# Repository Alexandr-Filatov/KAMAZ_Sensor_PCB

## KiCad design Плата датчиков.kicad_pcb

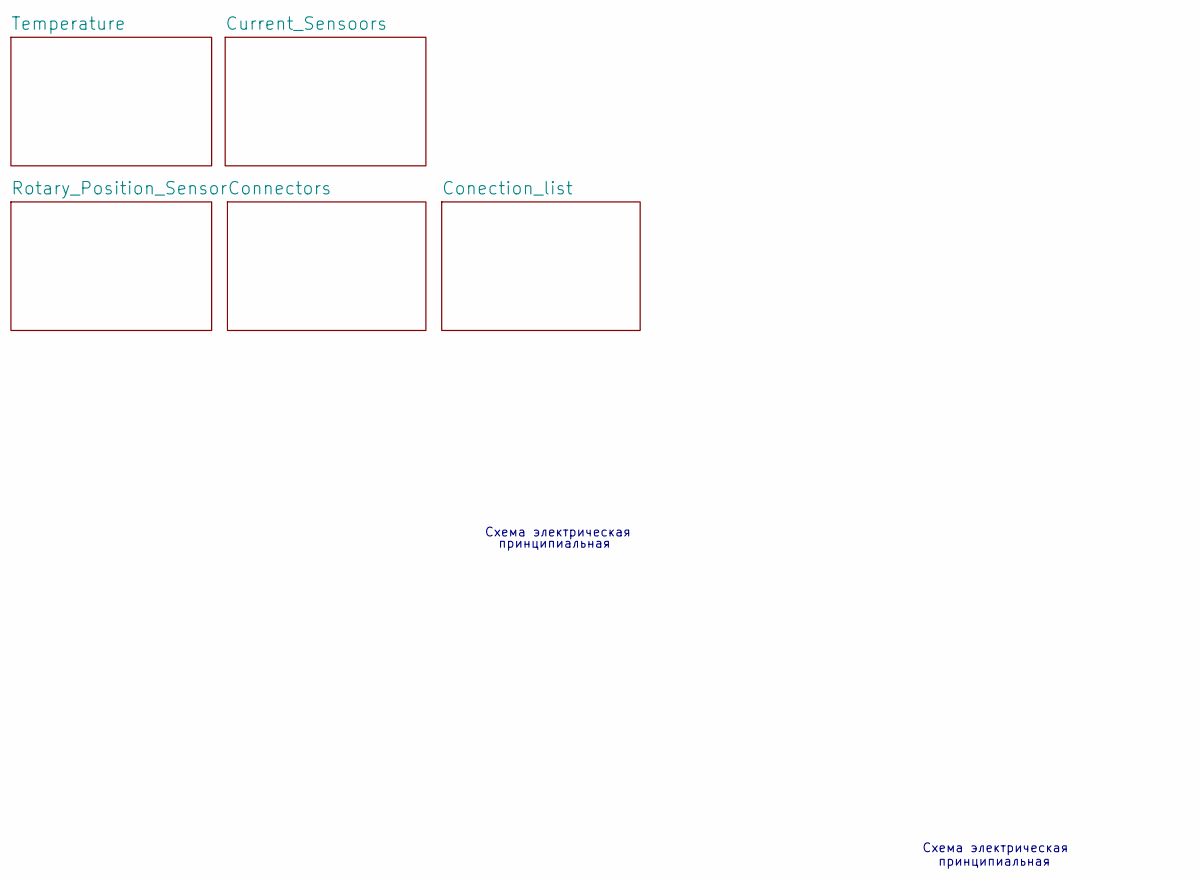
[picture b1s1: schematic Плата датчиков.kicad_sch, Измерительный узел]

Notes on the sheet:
Схема электрическая
принципиальная
Схема электрическая
принципиальная

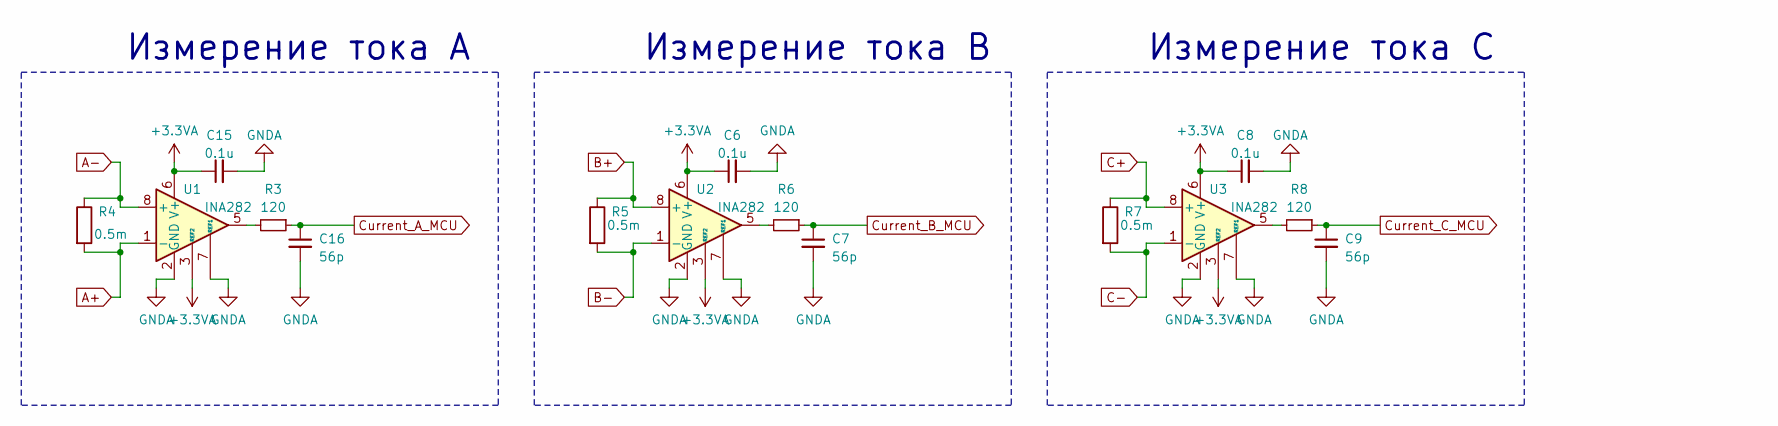
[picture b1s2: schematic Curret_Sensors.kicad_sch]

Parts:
C6, C8, C15: 0.1u; C_0603_1608Metric_Pad1.08x0.95mm_HandSolder
C7, C9, C16: 56p; C_0603_1608Metric_Pad1.08x0.95mm_HandSolder
R3, R6, R8: 120; R_0603_1608Metric_Pad0.98x0.95mm_HandSolder
R4, R5, R7: 0.5m; R_2512_6332Metric_Pad1.40x3.35mm_HandSolder
U1, U2, U3: INA282; SOIC-8_3.9x4.9mm_P1.27mm

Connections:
+3.3VA: C6.1, C8.1, C15.1, U1.3 (REF2), U1.6 (V+), U2.3 (REF2), U2.6 (V+), U3.3 (REF2), U3.6 (V+); also elsewhere on the board
A+: R4.2, U1.1 (-); also elsewhere on the board
A-: R4.1, U1.8 (+); also elsewhere on the board
B+: R5.1, U2.8 (+); also elsewhere on the board
B-: R5.2, U2.1 (-); also elsewhere on the board
C+: R7.1, U3.8 (+); also elsewhere on the board
C-: R7.2, U3.1 (-); also elsewhere on the board
Current_A_MCU: C16.1, R3.1; also elsewhere on the board
Current_B_MCU: C7.1, R6.1; also elsewhere on the board
Current_C_MCU: C9.1, R8.1; also elsewhere on the board
GNDA: C6.2, C7.2, C8.2, C9.2, C15.2, C16.2, U1.2 (GND), U1.7 (REF1), U2.2 (GND), U2.7 (REF1), U3.2 (GND), U3.7 (REF1); also elsewhere on the board
unnamed: R3.2, U1.5
unnamed: R6.2, U2.5
unnamed: R8.2, U3.5

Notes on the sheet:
Измерение тока В
Измерение тока А
Измерение тока С

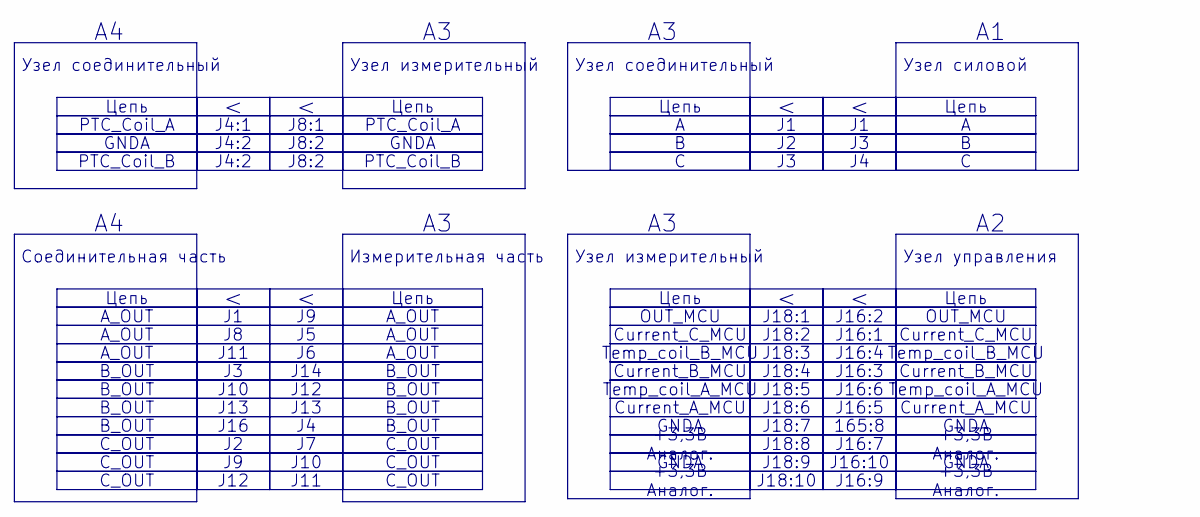
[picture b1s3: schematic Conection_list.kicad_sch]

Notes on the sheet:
J16
PTC_Coil_B
GNDA
Цепь
J18:4
165:8
J8:1
B_OUT
J18:10
J16:3
Current_B_MCU
J4:2
A_OUT
J16:5
OUT_MCU
Current_A_MCU
J16:9
J16:10
J18:8
J13
J10
PTC_Coil_A
J16:4
J12
+3,3В Аналог.
C_OUT
J11
J18:6
J18:5
J18:7
J12
J4:1
J8:2
Current_C_MCU
J16:6
Temp_coil_B_MCU
J10
J18:9
J18:2
J16:2

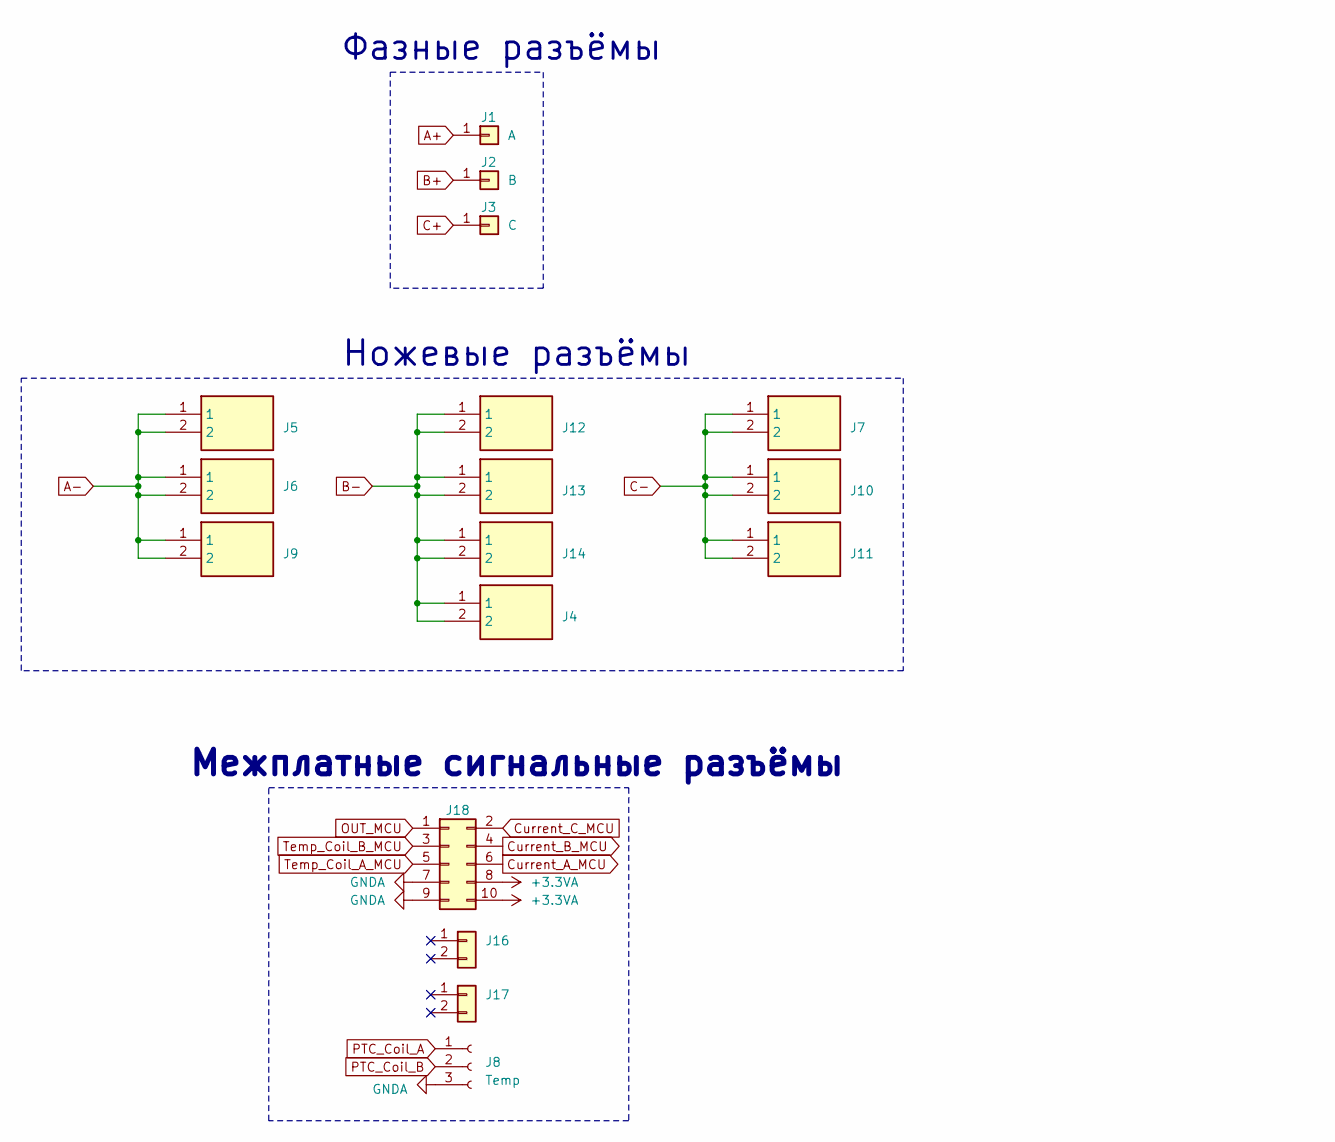
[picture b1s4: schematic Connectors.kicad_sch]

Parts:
J1: A; Power_Wire
J2: B; Power_Wire
J3: C; Power_Wire
J4, J5, J6, J7, J9, J10, J11, J12, J13, J14: 4900; Manufacturer_Part_Number 4900; Mouser Part Number 534-4900
J8: Temp; PinHeader_1x03_P2.54mm_Vertical
J16, J17: Conn_01x02; PinHeader_1x02_P1.27mm_Vertical
J18: Conn_02x05_Odd_Even; PinHeader_2x05_P1.27mm_Vertical

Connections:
+3.3VA: J18.8, J18.10; also elsewhere on the board
A+: J1.1; also elsewhere on the board
A-: J5.1, J5.2, J6.1, J6.2, J9.1, J9.2; also elsewhere on the board
B+: J2.1; also elsewhere on the board
B-: J4.1, J4.2, J12.1, J12.2, J13.1, J13.2, J14.1, J14.2; also elsewhere on the board
C+: J3.1; also elsewhere on the board
C-: J7.1, J7.2, J10.1, J10.2, J11.1, J11.2; also elsewhere on the board
Current_A_MCU: J18.6; also elsewhere on the board
Current_B_MCU: J18.4; also elsewhere on the board
Current_C_MCU: J18.2; also elsewhere on the board
GNDA: J8.3, J18.7, J18.9; also elsewhere on the board
OUT_MCU: J18.1; also elsewhere on the board
PTC_Coil_A: J8.1; also elsewhere on the board
PTC_Coil_B: J8.2; also elsewhere on the board
Temp_Coil_A_MCU: J18.5; also elsewhere on the board
Temp_Coil_B_MCU: J18.3; also elsewhere on the board

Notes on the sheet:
Межплатные сигнальные разъёмы
Фазные разъёмы
Ножевые разъёмы

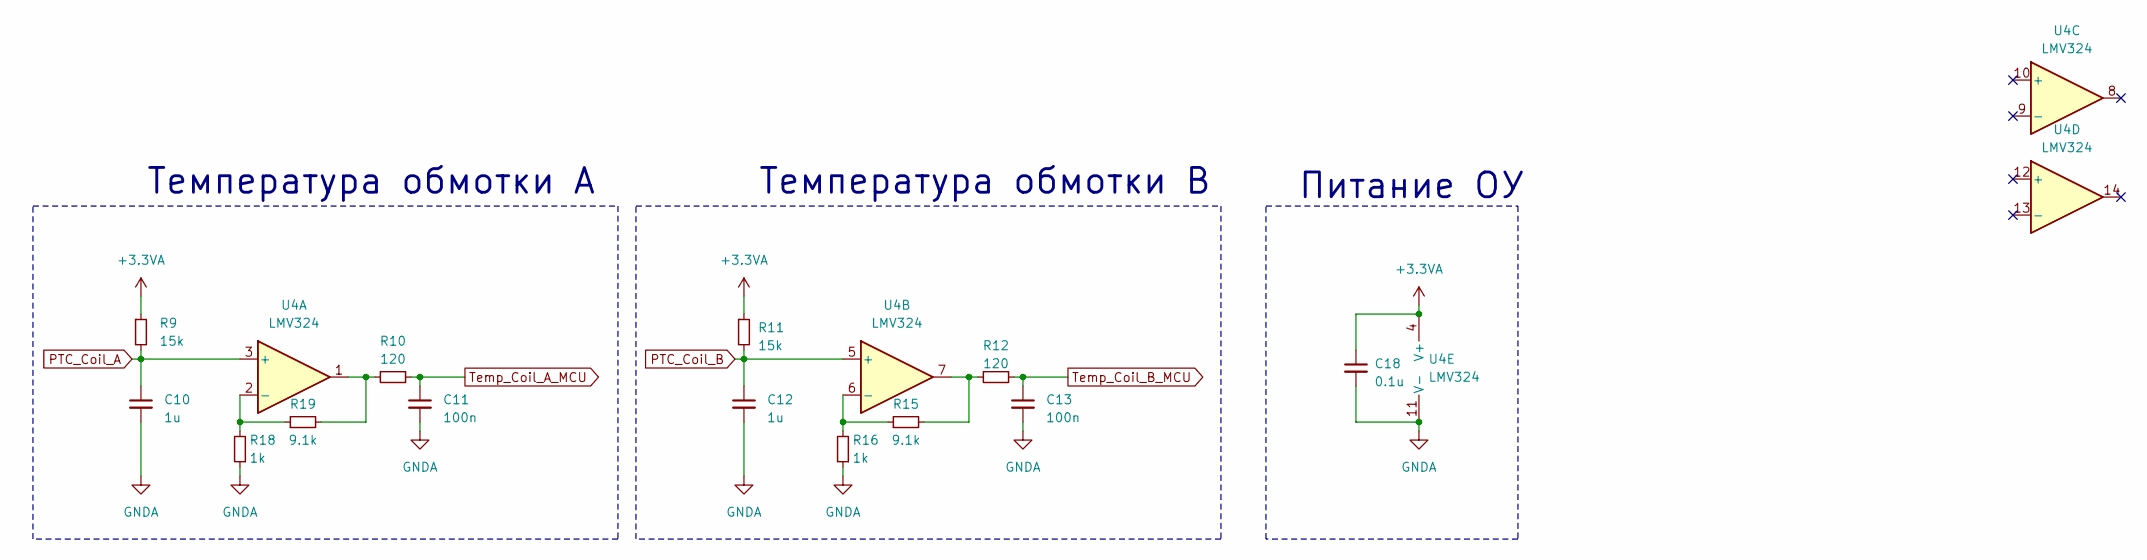
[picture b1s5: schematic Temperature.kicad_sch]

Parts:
C10, C12: 1u; C_0603_1608Metric_Pad1.08x0.95mm_HandSolder
C11, C13: 100n; C_0603_1608Metric_Pad1.08x0.95mm_HandSolder
C18: 0.1u; C_0603_1608Metric_Pad1.08x0.95mm_HandSolder
R9, R11: 15k; R_0603_1608Metric_Pad0.98x0.95mm_HandSolder
R10, R12: 120; R_0603_1608Metric_Pad0.98x0.95mm_HandSolder
R15, R19: 9.1k; R_0603_1608Metric_Pad0.98x0.95mm_HandSolder
R16, R18: 1k; R_0603_1608Metric_Pad0.98x0.95mm_HandSolder
U4: LMV324; SOIC-14_3.9x8.7mm_P1.27mm

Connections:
+3.3VA: C18.1, R9.1, R11.1, U4.4 (V+); also elsewhere on the board
GNDA: C10.2, C11.2, C12.2, C13.2, C18.2, R16.1, R18.1, U4.11 (V-); also elsewhere on the board
unnamed: R10.2, R19.2, U4.1
unnamed: R12.2, R15.2, U4.7
unnamed: R18.2, R19.1, U4.2 (-)
unnamed: R15.1, R16.2, U4.6 (-)
PTC_Coil_A: C10.1, R9.2, U4.3 (+); also elsewhere on the board
PTC_Coil_B: C12.1, R11.2, U4.5 (+); also elsewhere on the board
Temp_Coil_A_MCU: C11.1, R10.1; also elsewhere on the board
Temp_Coil_B_MCU: C13.1, R12.1; also elsewhere on the board

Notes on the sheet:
Температура обмотки B
Температура обмотки А
Питание ОУ

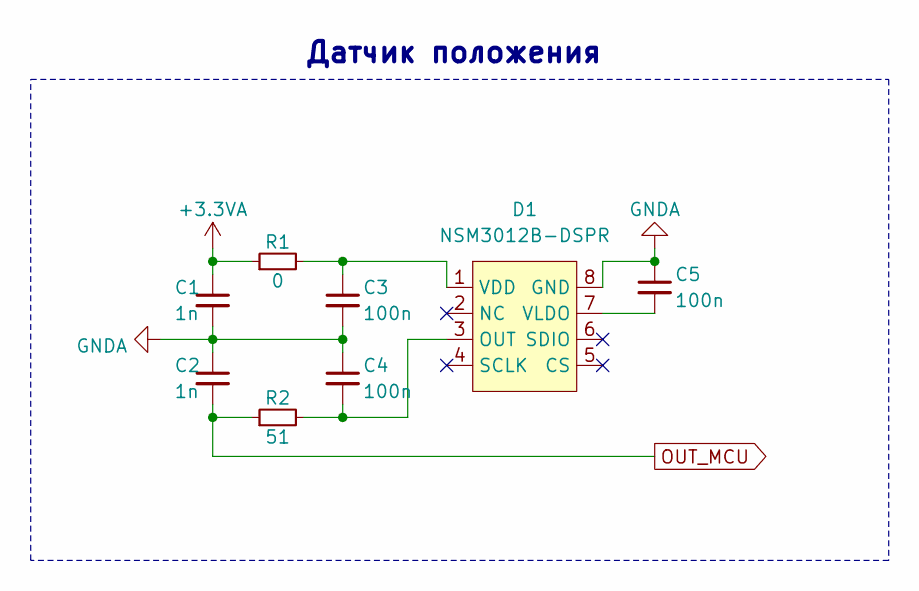
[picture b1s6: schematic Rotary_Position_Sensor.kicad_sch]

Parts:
C1, C2: 1n; C_0603_1608Metric_Pad1.08x0.95mm_HandSolder
C3, C4, C5: 100n; C_0603_1608Metric_Pad1.08x0.95mm_HandSolder
D1: NSM3012B-DSPR; SOIC-8_3.9x4.9mm_P1.27mm
R1: 0; R_0603_1608Metric_Pad0.98x0.95mm_HandSolder
R2: 51; R_0603_1608Metric_Pad0.98x0.95mm_HandSolder

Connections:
+3.3VA: C1.1, R1.1; also elsewhere on the board
GNDA: C1.2, C2.1, C3.2, C4.1, C5.1, D1.8 (GND); also elsewhere on the board
unnamed: C4.2, D1.3 (OUT), R2.2
unnamed: C3.1, D1.1 (VDD), R1.2
unnamed: C5.2, D1.7 (VLDO)
OUT_MCU: C2.2, R2.1; also elsewhere on the board

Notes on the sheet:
Датчик положения

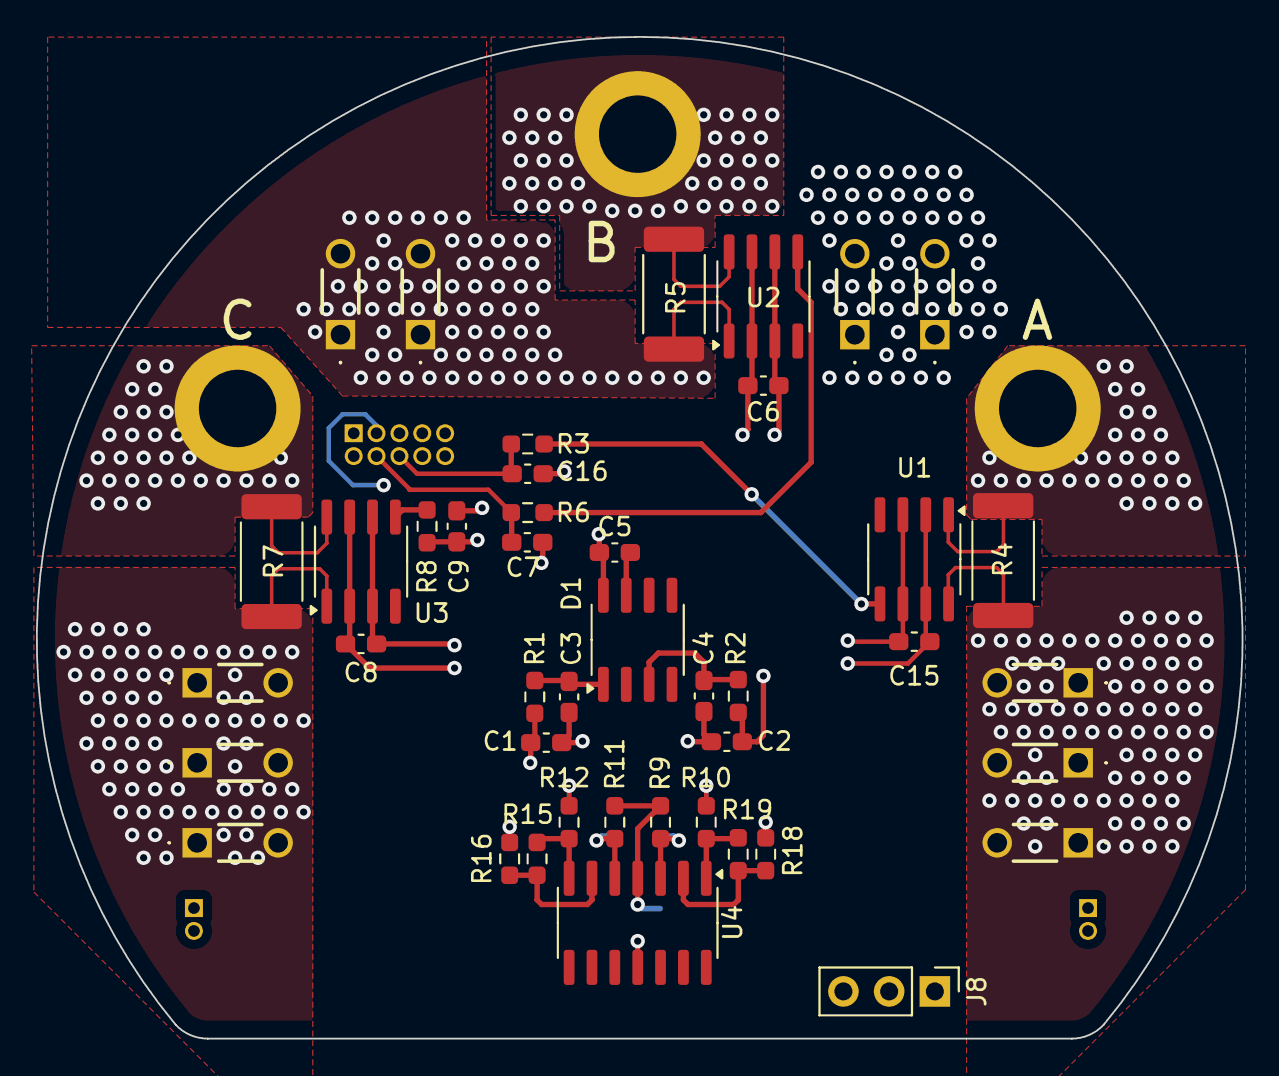
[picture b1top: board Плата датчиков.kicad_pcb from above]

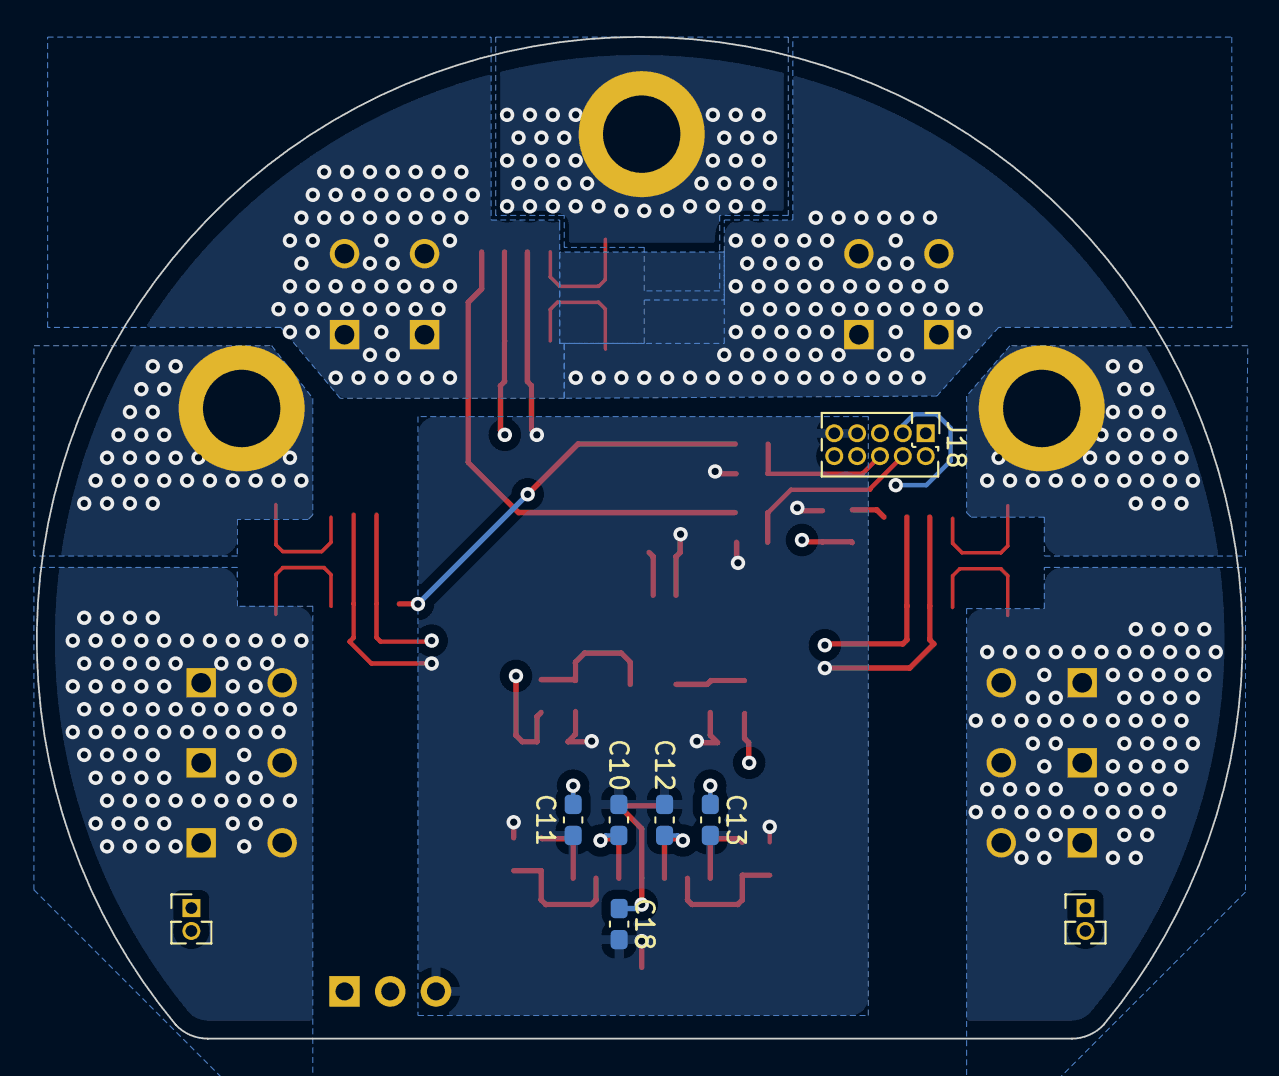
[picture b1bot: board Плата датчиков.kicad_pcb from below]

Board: 4 copper layers, 67.0 x 55.7 mm, 54 parts (8 on the bottom side), 26 nets.

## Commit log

2023-11-21 Нулевой коммит
2023-11-21 Расставил датчики на плате
2023-11-26 Изменил контур под новую крышку
2023-11-29 Поменял датчики на шунты
2023-11-29 Добавил разъёмы под обмотку
2023-11-29 Добавил модели разъёмов
2023-12-05 Переместил силовые разъёмы
2023-12-11 С ножевыми разъёмами по кругу
2023-12-11 Расставил ножевые разъмы финально
2023-12-12 Финальная доработка
2023-12-12 Ещё доработать
2023-12-14 Собираю документацию
2023-12-17 Добавил все документы
2023-12-24 Версия под отчёт
2024-06-04 Изменил разводку шунтов, вывел выход датчика положения после фильтра
2024-08-01 VER2.0
2024-09-26 Убрал лишние шунты
2024-09-29 Добавил разъёмы для крепления
2024-09-30 Добавил модель плты
2024-10-01 Добавил все в BOM
2024-10-02 Ничего не добавил
2024-10-03 Отправил на проверку в резонит
2024-10-11 Изменил резисторы подтяжки для PTC
2024-10-17 Zero comit
2024-10-17 Датчики тока NSM2015
2024-12-02 Изменения: добавил папку с отчетностью
